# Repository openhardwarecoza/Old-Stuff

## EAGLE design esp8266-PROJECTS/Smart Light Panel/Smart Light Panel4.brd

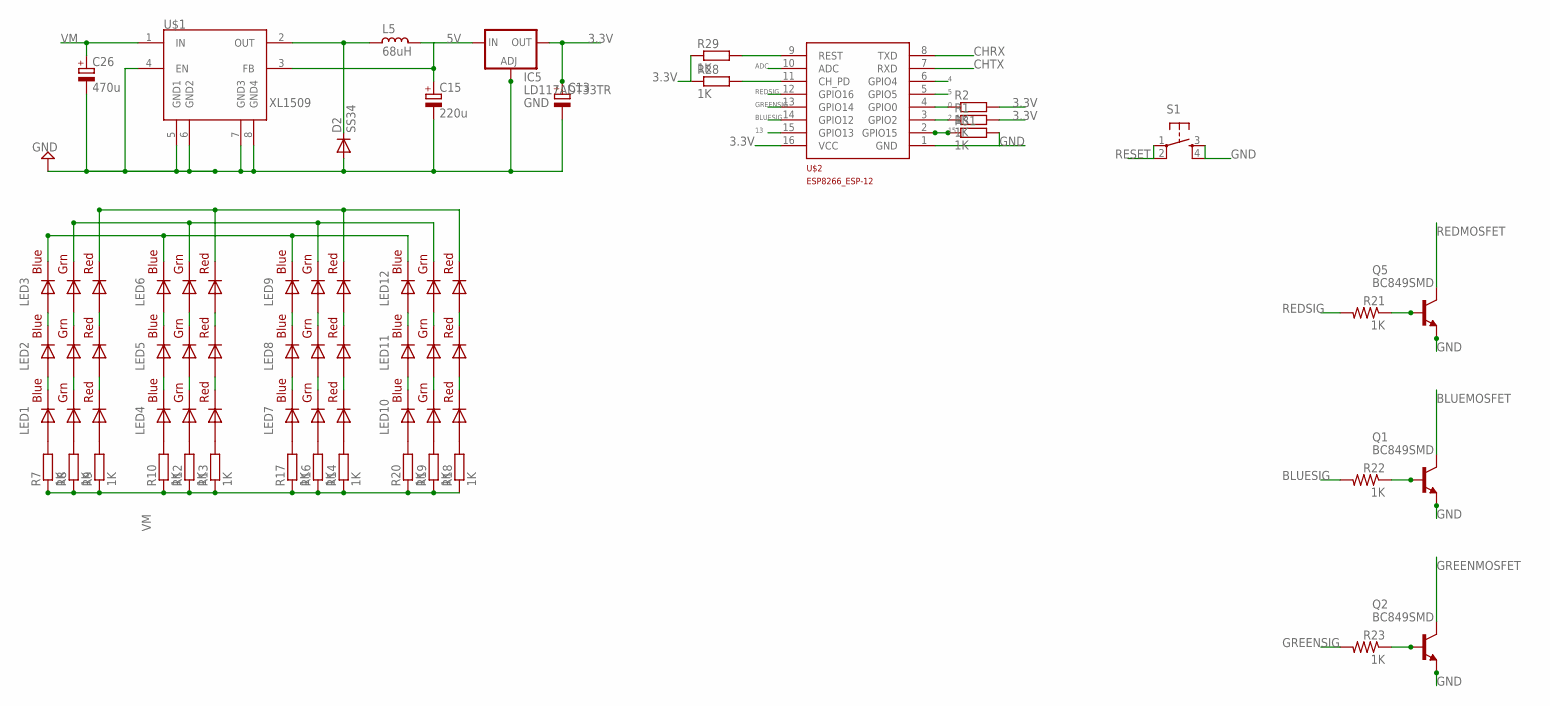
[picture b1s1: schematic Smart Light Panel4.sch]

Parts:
C13: CPOL-EUE2.5-7; E2,5-7
C15: 220u; E2,5-7
C26: 470u; E2,5-7
D2: SS34; DO-214AC
IC5: LD117ADT33TR; DPACK
L5: 68uH; CD75
LED1, LED2, LED3, LED4, LED5, LED6, LED7, LED8, LED9, LED10, LED11, LED12: RGBLED5050
Q1, Q2, Q5: BC849SMD; SOT23-BEC
R1, R2, R21, R22, R23, R28, R29, R31: 1K; M1206
R7, R8, R9, R10, R12, R13, R14, R16, R17, R18, R19, R20: 1K; R1206
S1: TAC_SWITCHPTH; TACTILE-PTH
U$1: XL1509; SO08
U$2: ESP8266_ESP-12; ESP8266-ESP12

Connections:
0: R2.1, U$2.4 (GPIO0)
2: R1.1, U$2.3 (GPIO2)
3.3V: C13.+, IC5.4 (OUT), R1.2, R2.2, R28.1, R29.1, U$2.16 (VCC)
4: U$2.6 (GPIO4)
5: U$2.5 (GPIO5)
5V: C15.+, IC5.3 (IN), L5.1, U$1.3 (FB)
13: U$2.15 (GPIO13)
15: R31.1, U$2.2 (GPIO15)
ADC: U$2.10 (ADC)
BLUEMOSFET: LED3.4 (BLUE_C), LED6.4 (BLUE_C), LED9.4 (BLUE_C), LED12.4 (BLUE_C), Q1.C
BLUESIG: R22.2, U$2.14 (GPIO12)
CHRX: U$2.8 (TXD)
CHTX: U$2.7 (RXD)
GND: C13.-, C15.-, C26.-, D2.2 (A), IC5.1 (ADJ), Q1.E, Q2.E, Q5.E, R31.2, S1.3, S1.4, U$1.4 (EN), U$1.5 (GND1), U$1.6 (GND2), U$1.7 (GND3), U$1.8 (GND4), U$2.1 (GND)
GREENMOSFET: LED3.6 (GREEN_C), LED6.6 (GREEN_C), LED9.6 (GREEN_C), LED12.6 (GREEN_C), Q2.C
GREENSIG: R23.2, U$2.13 (GPIO14)
unnamed: LED2.4 (BLUE_C), LED3.3 (BLUE_A)
unnamed: LED2.6 (GREEN_C), LED3.1 (GREEN_A)
unnamed: Q1.B, R22.1
unnamed: LED2.5 (RED_C), LED3.2 (RED_A)
unnamed: LED1.5 (RED_C), LED2.2 (RED_A)
unnamed: Q2.B, R23.1
unnamed: LED1.6 (GREEN_C), LED2.1 (GREEN_A)
unnamed: LED1.4 (BLUE_C), LED2.3 (BLUE_A)
unnamed: LED4.4 (BLUE_C), LED5.3 (BLUE_A)
unnamed: LED4.6 (GREEN_C), LED5.1 (GREEN_A)
unnamed: LED5.4 (BLUE_C), LED6.3 (BLUE_A)
unnamed: R28.2, U$2.11 (CH_PD)
unnamed: LED5.6 (GREEN_C), LED6.1 (GREEN_A)
unnamed: LED4.5 (RED_C), LED5.2 (RED_A)
unnamed: LED5.5 (RED_C), LED6.2 (RED_A)
unnamed: LED7.4 (BLUE_C), LED8.3 (BLUE_A)
unnamed: LED8.4 (BLUE_C), LED9.3 (BLUE_A)
unnamed: LED7.6 (GREEN_C), LED8.1 (GREEN_A)
unnamed: LED8.6 (GREEN_C), LED9.1 (GREEN_A)
unnamed: LED7.5 (RED_C), LED8.2 (RED_A)
unnamed: LED8.5 (RED_C), LED9.2 (RED_A)
unnamed: LED10.4 (BLUE_C), LED11.3 (BLUE_A)
unnamed: LED11.4 (BLUE_C), LED12.3 (BLUE_A)
unnamed: LED10.6 (GREEN_C), LED11.1 (GREEN_A)
unnamed: LED11.6 (GREEN_C), LED12.1 (GREEN_A)
unnamed: LED10.5 (RED_C), LED11.2 (RED_A)
unnamed: LED11.5 (RED_C), LED12.2 (RED_A)
unnamed: Q5.B, R21.1
unnamed: D2.1 (C), L5.2, U$1.2 (OUT)
unnamed: LED1.3 (BLUE_A), R7.2
unnamed: LED1.1 (GREEN_A), R8.2
unnamed: LED1.2 (RED_A), R9.2
unnamed: LED4.3 (BLUE_A), R10.2
unnamed: LED4.1 (GREEN_A), R12.2
unnamed: LED4.2 (RED_A), R13.2
unnamed: LED7.2 (RED_A), R14.2
unnamed: LED7.1 (GREEN_A), R16.2
unnamed: LED7.3 (BLUE_A), R17.2
unnamed: LED10.2 (RED_A), R18.2
unnamed: LED10.1 (GREEN_A), R19.2
unnamed: LED10.3 (BLUE_A), R20.2
REDMOSFET: LED3.5 (RED_C), LED6.5 (RED_C), LED9.5 (RED_C), LED12.5 (RED_C), Q5.C
REDSIG: R21.2, U$2.12 (GPIO16)
RESET: R29.2, S1.1, S1.2, U$2.9 (REST)
VM: C26.+, R7.1, R8.1, R9.1, R10.1, R12.1, R13.1, R14.1, R16.1, R17.1, R18.1, R19.1, R20.1, U$1.1 (IN)

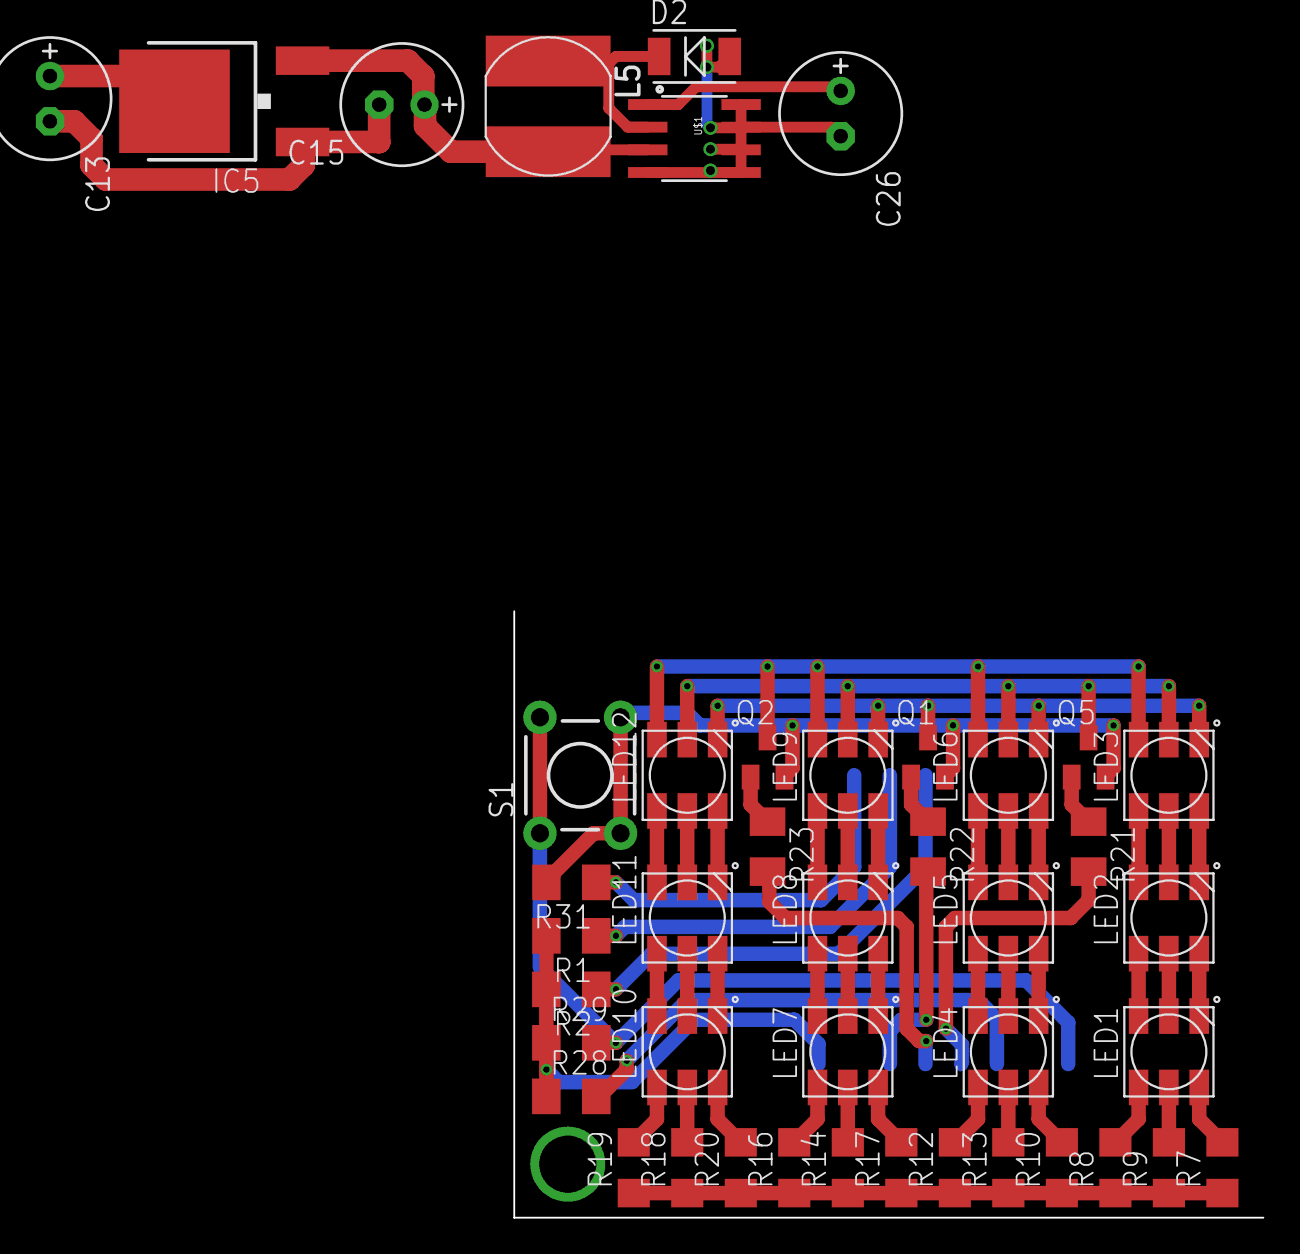
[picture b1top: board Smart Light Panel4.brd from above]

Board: 2 copper layers, 42.0 x 34.0 mm, 44 parts (1 on the bottom side), 55 nets.

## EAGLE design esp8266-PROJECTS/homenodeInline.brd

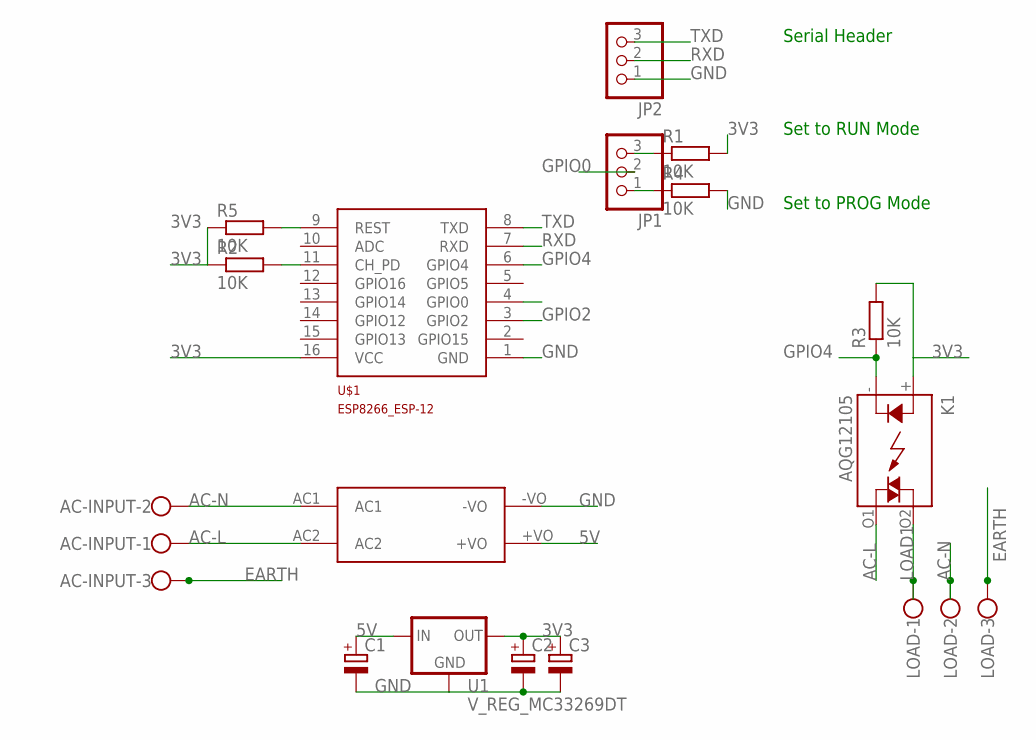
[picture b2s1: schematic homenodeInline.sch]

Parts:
AC-INPUT: W237-103
C1, C2, C3: CPOL-EUC; PANASONIC_C
JP1, JP2: PINHD-1X3; 1X03
K1: AQG12105; AQG
LOAD: W237-103
R1, R2, R3, R4, R5: 10K; M1206
U1: V_REG_MC33269DT; DPAK
U$1: ESP8266_ESP-12; ESP8266-ESP12
U$4: HLK-PM01

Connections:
3V3: C2.+, C3.+, K1.+ (A), R1.2, R2.1, R3.2, R5.1, U1.4 (OUT), U$1.16 (VCC)
5V: C1.+, U1.3 (IN), U$4.+VO
AC-L: AC-INPUT.1, K1.O1 (DS2), U$4.AC2
AC-N: AC-INPUT.2, LOAD.2, U$4.AC1
CH_PD: R2.2, U$1.11 (CH_PD)
EARTH: AC-INPUT.3, LOAD.3
GND: C1.-, C2.-, C3.-, JP2.1, R4.2, U1.1 (GND), U$1.1 (GND), U$4.-VO
GPIO0: JP1.2, U$1.4 (GPIO0)
GPIO2: U$1.3 (GPIO2)
GPIO4: K1.- (K), R3.1, U$1.6 (GPIO4)
LOAD1: K1.O2 (DS1), LOAD.1
unnamed: JP1.3, R1.1
unnamed: JP1.1, R4.1
unnamed: R5.2, U$1.9 (REST)
RXD: JP2.2, U$1.7 (RXD)
TXD: JP2.3, U$1.8 (TXD)

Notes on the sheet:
Set to RUN Mode
Set to PROG Mode
Serial Header

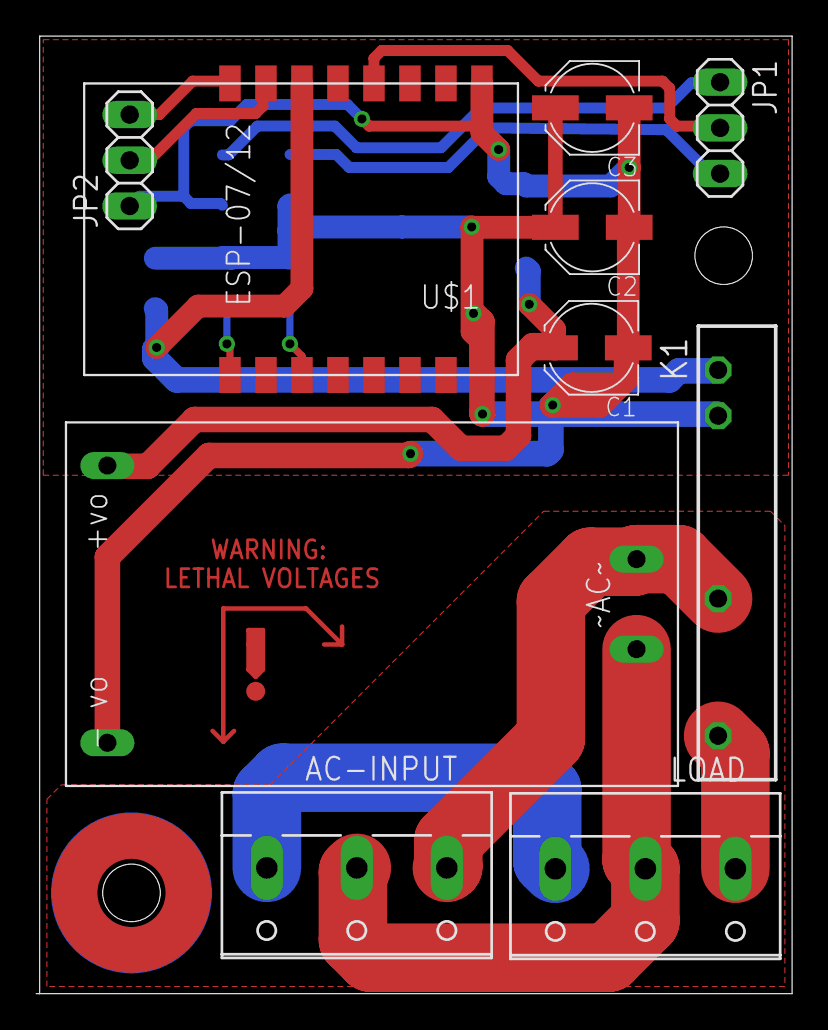
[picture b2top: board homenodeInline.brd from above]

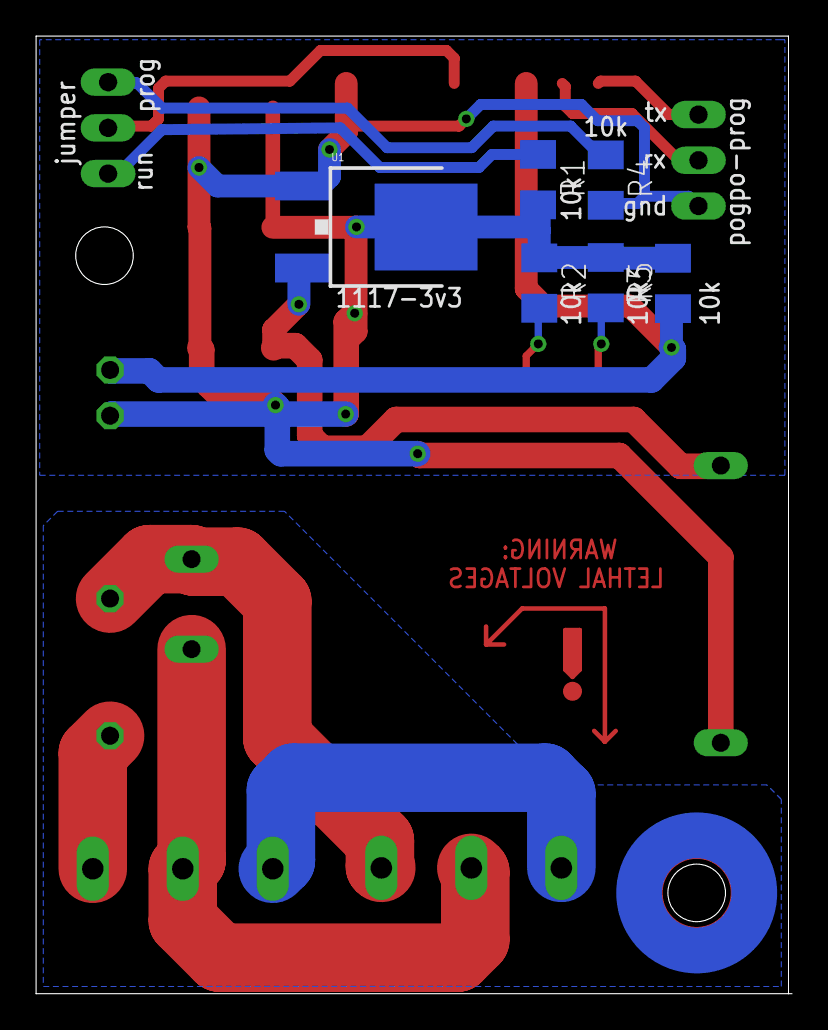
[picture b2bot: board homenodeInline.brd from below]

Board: 2 copper layers, 41.8 x 53.2 mm, 16 parts (6 on the bottom side), 15 nets.

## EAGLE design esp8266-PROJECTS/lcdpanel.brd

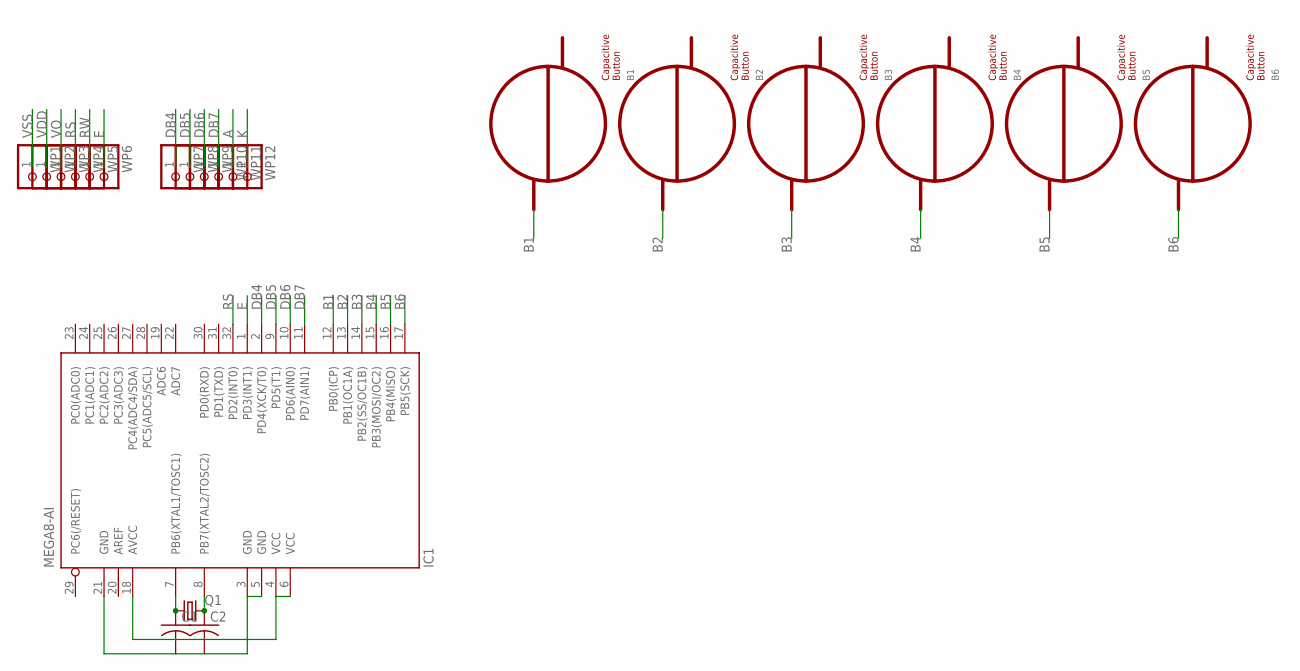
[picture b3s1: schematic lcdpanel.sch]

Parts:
B1, B2, B3, B4, B5, B6: BUTTON_ACTIVE_DUAL; BUTTON_ACTIVE_DUAL_10MM
C1, C2: C-USC1206; C1206
IC1: MEGA8-AI; TQFP32-08
Q1: CRYSTALHC49UP; HC49UP
WP1, WP2, WP3, WP4, WP5, WP6, WP7, WP8, WP9, WP10, WP11, WP12: WPAD-1-0805

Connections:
A: WP11.1
B1: B1.Q2, IC1.12 (PB0(ICP))
B2: B2.Q2, IC1.13 (PB1(OC1A))
B3: B3.Q2, IC1.14 (PB2(SS/OC1B))
B4: B4.Q2, IC1.15 (PB3(MOSI/OC2))
B5: B5.Q2, IC1.16 (PB4(MISO))
B6: B6.Q2, IC1.17 (PB5(SCK))
DB4: IC1.2 (PD4(XCK/T0)), WP7.1
DB5: IC1.9 (PD5(T1)), WP8.1
DB6: IC1.10 (PD6(AIN0)), WP9.1
DB7: IC1.11 (PD7(AIN1)), WP10.1
E: IC1.1 (PD3(INT1)), WP6.1
K: WP12.1
unnamed: C2.1, IC1.8 (PB7(XTAL2/TOSC2)), Q1.2
unnamed: C1.1, IC1.7 (PB6(XTAL1/TOSC1)), Q1.1
unnamed: C1.2, C2.2, IC1.3 (GND), IC1.5 (GND), IC1.21 (GND)
unnamed: IC1.4 (VCC), IC1.6 (VCC), IC1.18 (AVCC)
RS: IC1.32 (PD2(INT0)), WP4.1
RW: WP5.1
VDD: WP2.1
VO: WP3.1
VSS: WP1.1

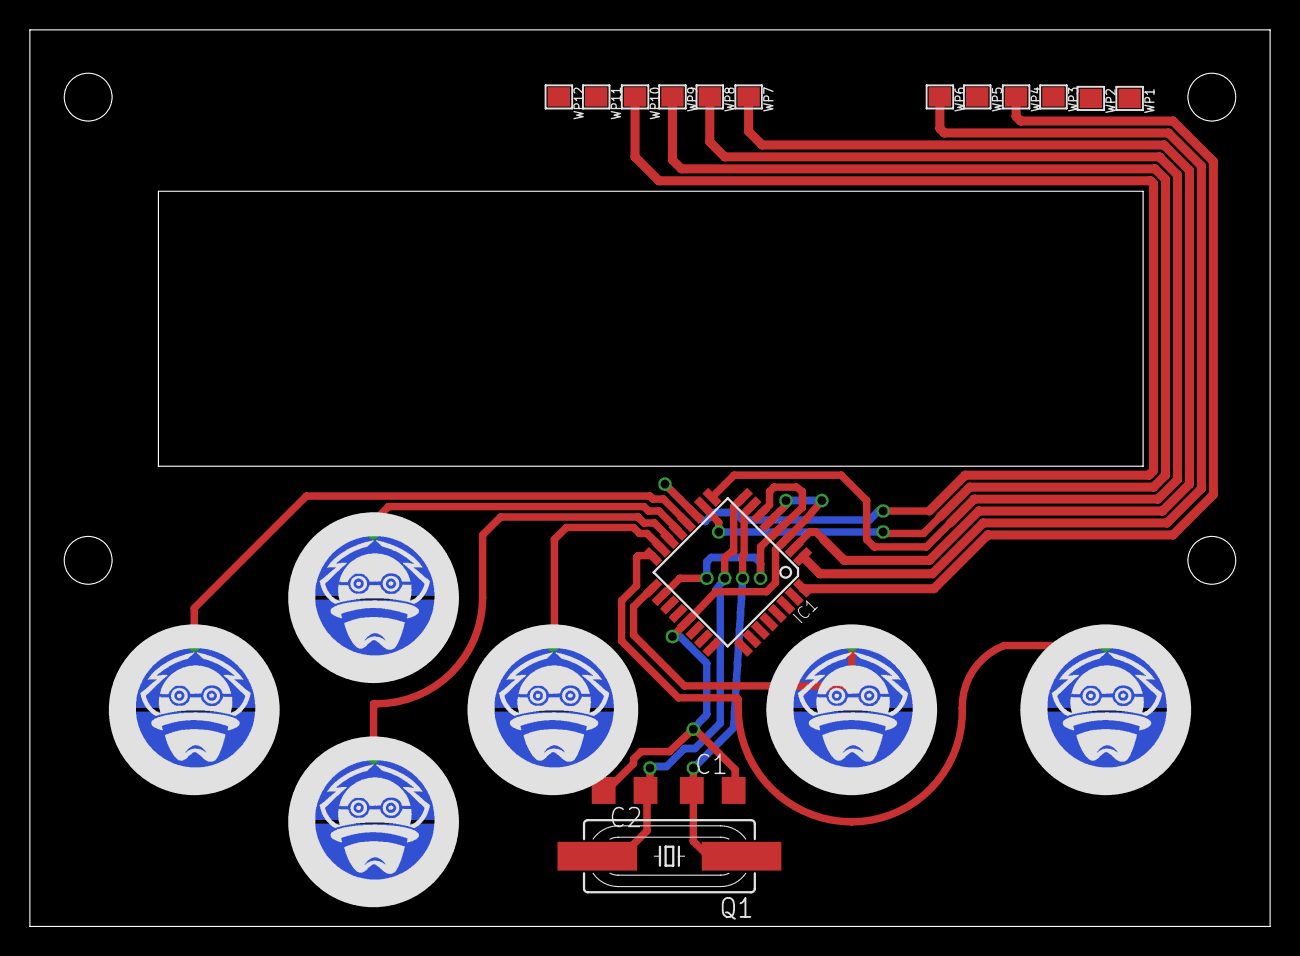
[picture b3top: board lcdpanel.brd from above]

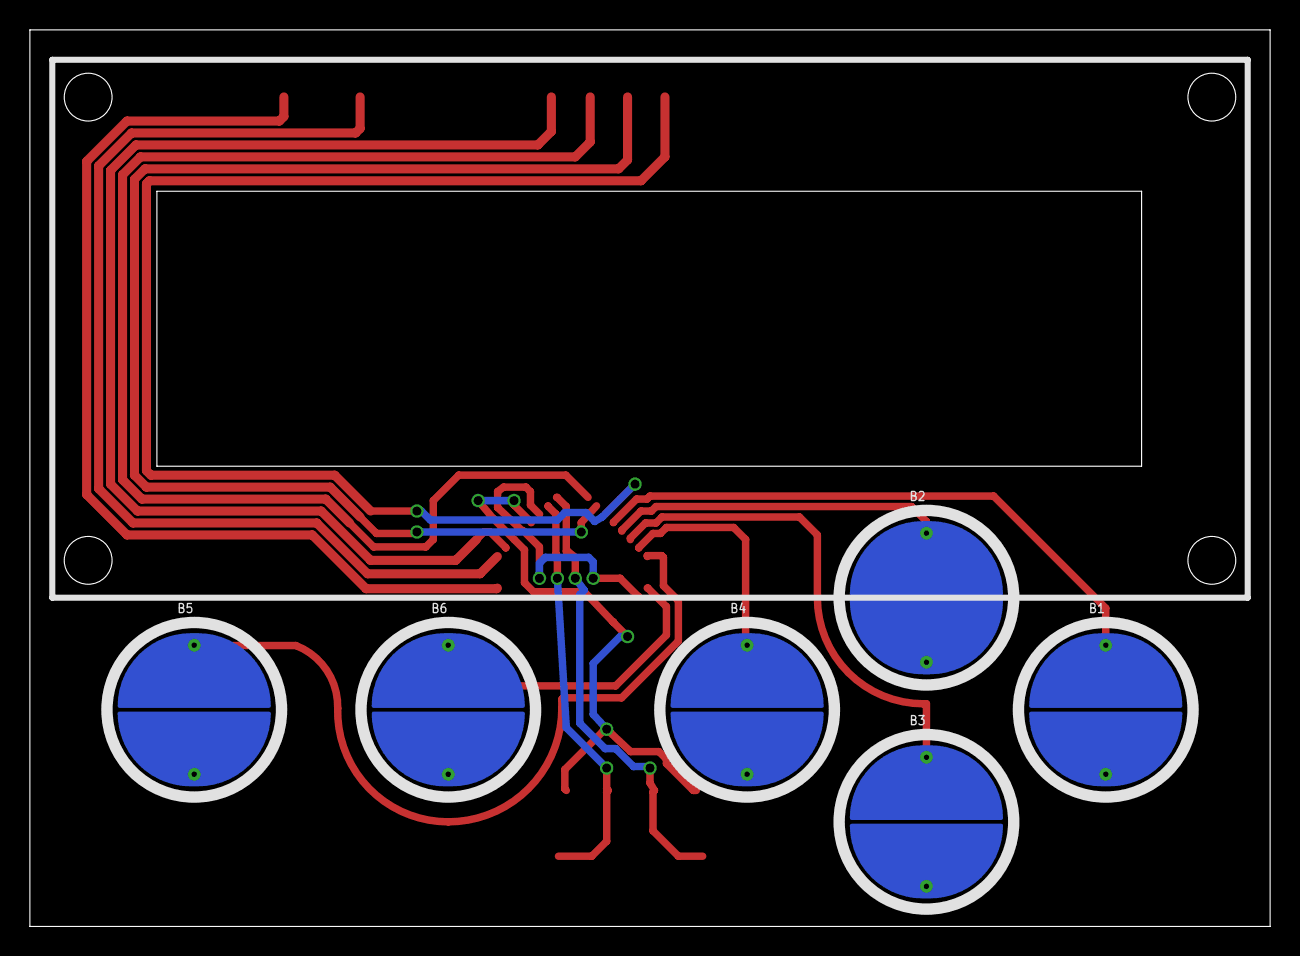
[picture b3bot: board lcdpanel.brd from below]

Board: 2 copper layers, 83.0 x 60.0 mm, 22 parts (6 on the bottom side), 16 nets.

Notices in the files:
parts and their libraries:
rc-master-smd: Copyright (C) 2007, Bob Starr
SparkFun-PowerIC: Licensing: Creative Commons ShareAlike 4.0 International - https://creativecommons.org/licenses/by-sa/4.0
PatternAgents-TouchWidgets: License : http://creativecommons.org/licenses/by-sa/4.0/ (Creative Commons 4.0)
